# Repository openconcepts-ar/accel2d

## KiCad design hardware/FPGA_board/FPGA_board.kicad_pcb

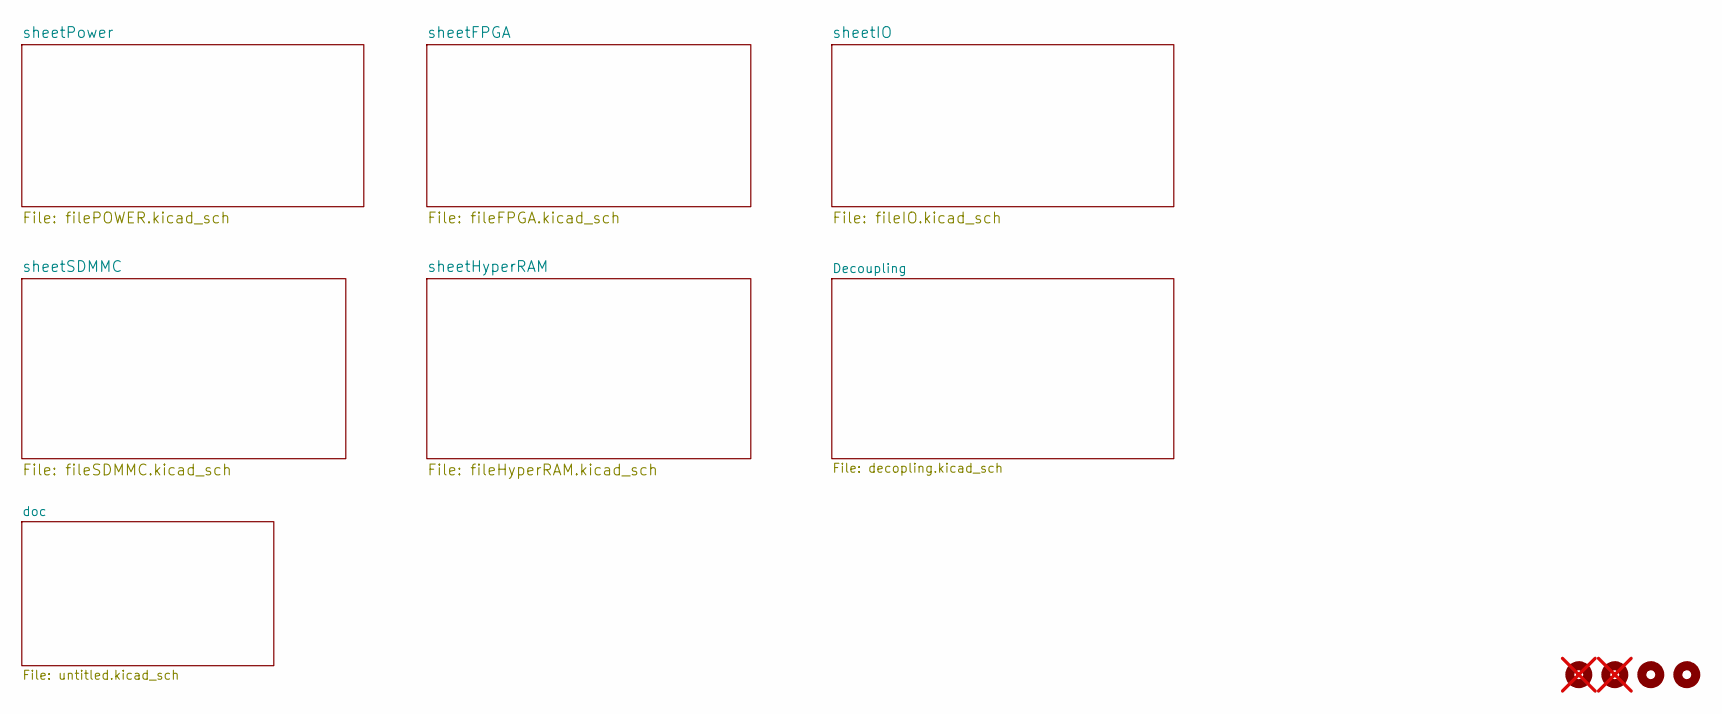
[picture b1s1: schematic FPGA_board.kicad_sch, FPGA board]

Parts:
H1, H2: MountingHole; MountingHole_2.2mm_M2_Pad; not fitted
H3, H4: MountingHole; MountingHole_2.1mm

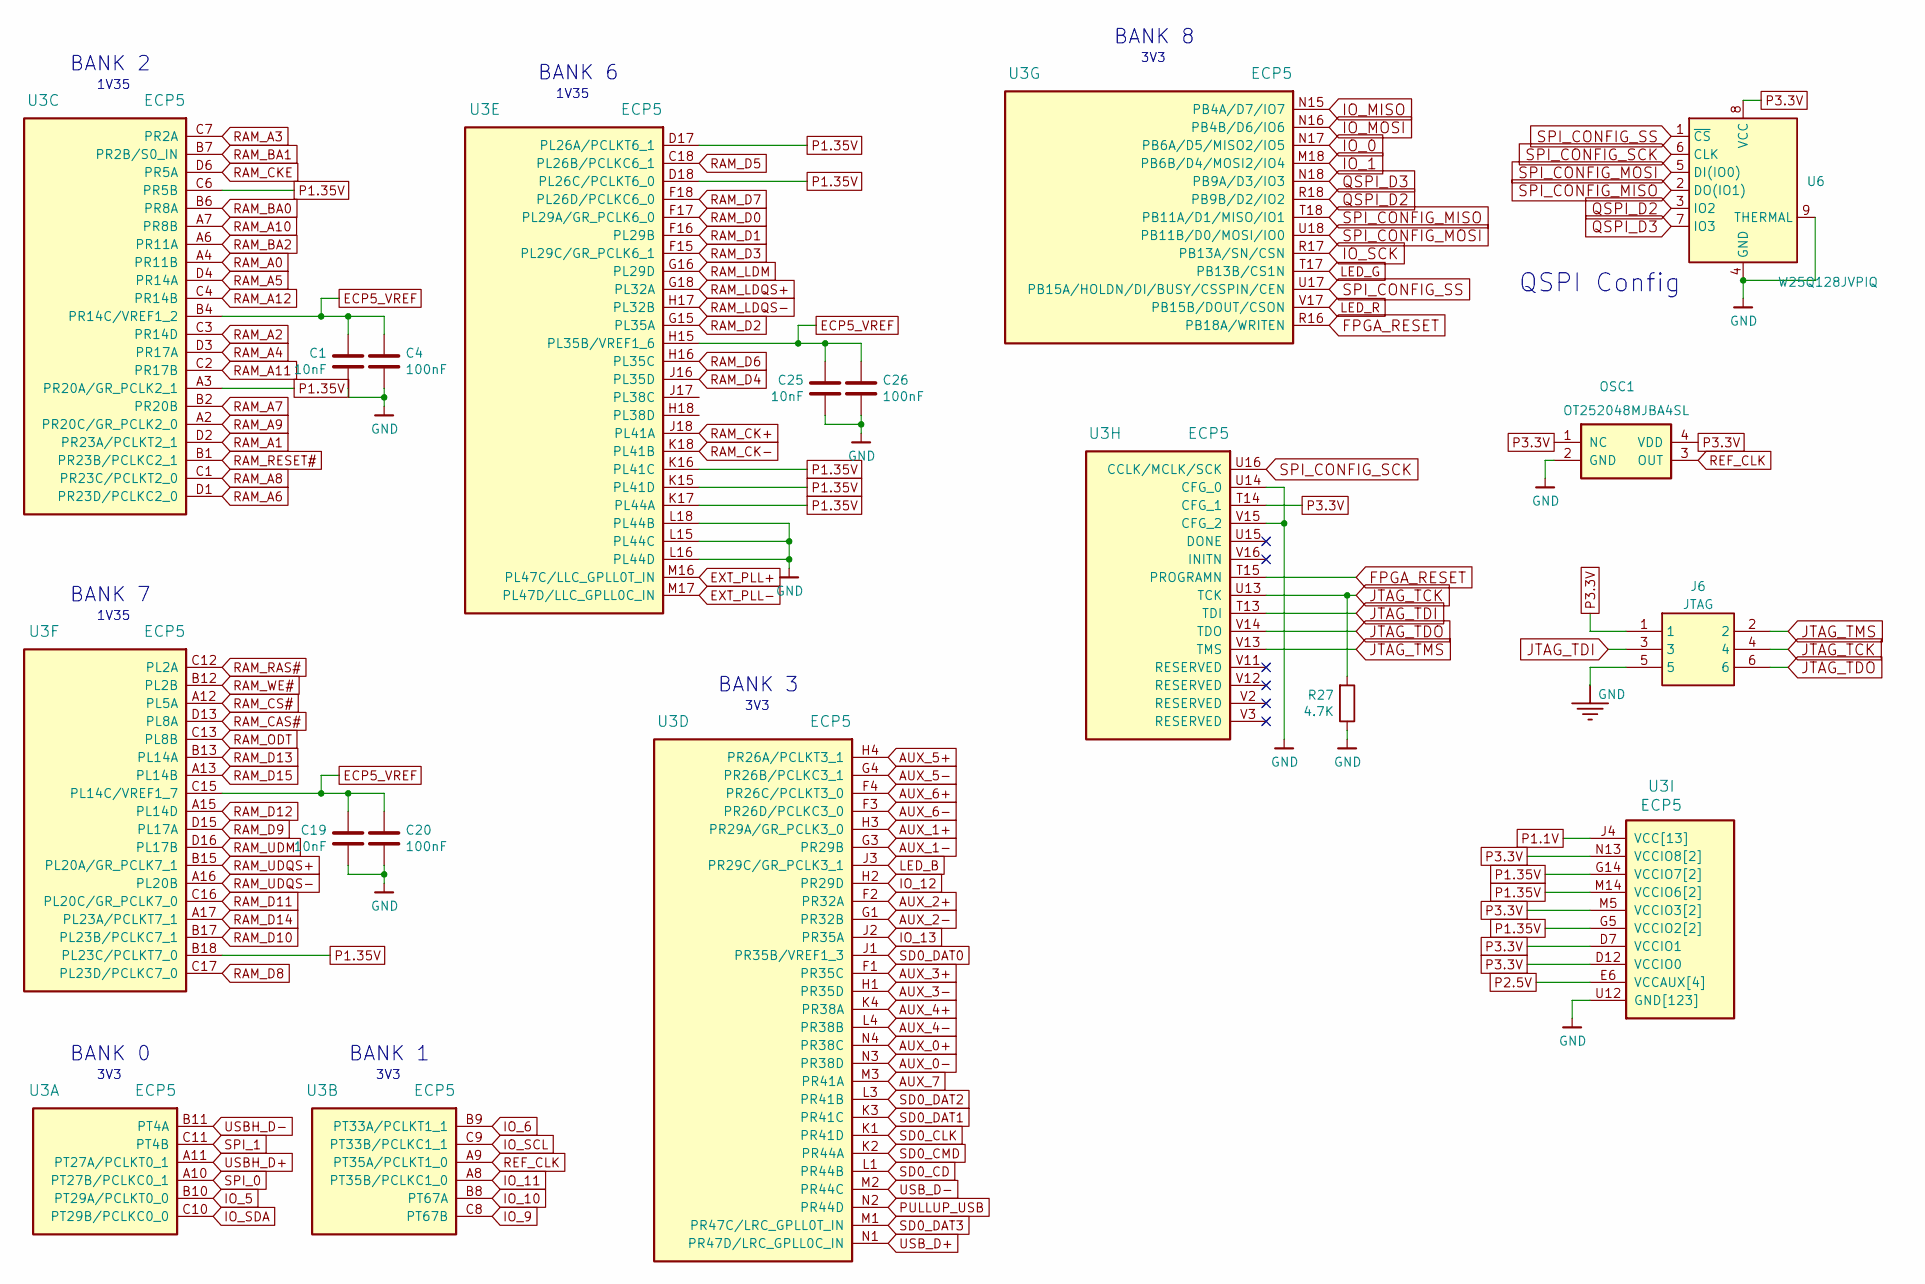
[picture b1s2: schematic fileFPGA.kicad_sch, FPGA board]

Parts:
C1, C19, C25: 10nF; C_0201_0603Metric; MPN GRM033R61C103KA12D
C4, C20, C26: 100nF; C_0201_0603Metric; MPN CL03A104KQ3NNNC
J6: JTAG; Tag-Connect_TC2030-IDC-NL_2x03_P1.27mm_Vertical; Mouser Part Number 474-PRT-12807; LCSC Part Number DNP
OSC1: OT252048MJBA4SL; Oscilator_2.5x2.0; MPN OT252048MJBA4SL
R27: 4.7K; R_0201_0603Metric; MPN RC0201FR-074K7L
U3: ECP5; csBGA285; MPN LFE5U-85F-8MG285I
U6: W25Q128JVPIQ; WSON-8-1EP_6x5mm_P1.27mm_EP3.4x4.3mm; MPN W25Q128JVPIQ

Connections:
AUX_0+: U3.N4 (PR38C); also elsewhere on the board
AUX_0-: U3.N3 (PR38D); also elsewhere on the board
AUX_1+: U3.H3 (PR29A/GR_PCLK3_0); also elsewhere on the board
AUX_1-: U3.G3 (PR29B); also elsewhere on the board
AUX_2+: U3.F2 (PR32A); also elsewhere on the board
AUX_2-: U3.G1 (PR32B); also elsewhere on the board
AUX_3+: U3.F1 (PR35C); also elsewhere on the board
AUX_3-: U3.H1 (PR35D); also elsewhere on the board
AUX_4+: U3.K4 (PR38A); also elsewhere on the board
AUX_4-: U3.L4 (PR38B); also elsewhere on the board
AUX_5+: U3.H4 (PR26A/PCLKT3_1); also elsewhere on the board
AUX_5-: U3.G4 (PR26B/PCLKC3_1); also elsewhere on the board
AUX_6+: U3.F4 (PR26C/PCLKT3_0); also elsewhere on the board
AUX_6-: U3.F3 (PR26D/PCLKC3_0); also elsewhere on the board
AUX_7: U3.M3 (PR41A); also elsewhere on the board
ECP5_VREF: C1.1, C4.1, C19.1, C20.1, C25.1, C26.1, U3.B4 (PR14C/VREF1_2), U3.C15 (PL14C/VREF1_7), U3.H15 (PL35B/VREF1_6); also elsewhere on the board
EXT_PLL+: U3.M16 (PL47C/LLC_GPLL0T_IN); also elsewhere on the board
EXT_PLL-: U3.M17 (PL47D/LLC_GPLL0C_IN); also elsewhere on the board
FPGA_RESET: U3.R16 (PB18A/WRITEN), U3.T15 (PROGRAMN); also elsewhere on the board
GND: C1.2, C4.2, C19.2, C20.2, C25.2, C26.2, J6.5, OSC1.2 (GND), R27.1, U3.B3 (GND[123]), U3.B16 (GND[123]), U3.E5 (GND[123]), U3.E7 (GND[123]), U3.E8 (GND[123]), U3.E9 (GND[123]), U3.E10 (GND[123]), U3.E11 (GND[123]), U3.E12 (GND[123]), U3.E14 (GND[123]), U3.F5 (GND[123]), U3.F6 (GND[123]), U3.F7 (GND[123]), U3.F8 (GND[123]), U3.F9 (GND[123]), U3.F10 (GND[123]), U3.F11 (GND[123]), U3.F12 (GND[123]), U3.F13 (GND[123]), U3.F14 (GND[123]), U3.G2 (GND[123]), U3.G6 (GND[123]), U3.G7 (GND[123]), U3.G8 (GND[123]), U3.G9 (GND[123]), U3.G10 (GND[123]), U3.G11 (GND[123]), U3.G12 (GND[123]), U3.G13 (GND[123]), U3.G17 (GND[123]), U3.H6 (GND[123]), U3.H7 (GND[123]), U3.H8 (GND[123]), U3.H9 (GND[123]), U3.H10 (GND[123]), U3.H11 (GND[123]), U3.H12 (GND[123]), U3.H13 (GND[123]), U3.J6 (GND[123]), U3.J7 (GND[123]), U3.J8 (GND[123]), U3.J9 (GND[123]), U3.J10 (GND[123]), U3.J11 (GND[123]), U3.J12 (GND[123]), U3.J13 (GND[123]), U3.K5 (GND[123]), U3.K6 (GND[123]), U3.K7 (GND[123]), U3.K8 (GND[123]), U3.K9 (GND[123]), U3.K10 (GND[123]), U3.K11 (GND[123]), U3.K12 (GND[123]), U3.K13 (GND[123]), U3.K14 (GND[123]), U3.L2 (GND[123]), U3.L5 (GND[123]), U3.L6 (GND[123]), U3.L7 (GND[123]), U3.L8 (GND[123]), U3.L9 (GND[123]), U3.L10 (GND[123]), U3.L11 (GND[123]), U3.L12 (GND[123]), U3.L13 (GND[123]), U3.L14 (GND[123]), U3.L15 (PL44C), U3.L16 (PL44D), U3.L17 (GND[123]), U3.L18 (PL44B), U3.M6 (GND[123]), U3.M7 (GND[123]), U3.M8 (GND[123]), U3.M9 (GND[123]), U3.M10 (GND[123]), U3.M11 (GND[123]), U3.M12 (GND[123]), U3.M13 (GND[123]), U3.N7 (GND[123]), U3.N8 (GND[123]), U3.N9 (GND[123]), U3.N10 (GND[123]), U3.N11 (GND[123]), U3.N12 (GND[123]), U3.P5 (GND[123]), U3.P6 (GND[123]), U3.P8 (GND[123]), U3.P10 (GND[123]), U3.P12 (GND[123]), U3.R1 (GND[123]), U3.R2 (GND[123]), U3.R3 (GND[123]), U3.R10 (GND[123]), U3.T1 (GND[123]), U3.T2 (GND[123]), U3.T3 (GND[123]), U3.T4 (GND[123]), U3.T5 (GND[123]), U3.T6 (GND[123]), U3.T7 (GND[123]), U3.T8 (GND[123]), U3.T9 (GND[123]), U3.T10 (GND[123]), U3.T11 (GND[123]), U3.T12 (GND[123]), U3.T16 (GND[123]), U3.U1 (GND[123]), U3.U2 (GND[123]), U3.U3 (GND[123]), U3.U4 (GND[123]), U3.U5 (GND[123]), U3.U6 (GND[123]), U3.U7 (GND[123]), U3.U8 (GND[123]), U3.U9 (GND[123]), U3.U10 (GND[123]), U3.U11 (GND[123]), U3.U12 (GND[123]), U3.U14 (CFG_0), U3.V4 (GND[123]), U3.V5 (GND[123]), U3.V6 (GND[123]), U3.V7 (GND[123]), U3.V8 (GND[123]), U3.V9 (GND[123]), U3.V10 (GND[123]), U3.V15 (CFG_2), U6.4 (GND), U6.9 (THERMAL); also elsewhere on the board
IO_0: U3.N17 (PB6A/D5/MISO2/IO5); also elsewhere on the board
IO_1: U3.M18 (PB6B/D4/MOSI2/IO4); also elsewhere on the board
IO_5: U3.B10 (PT29A/PCLKT0_0); also elsewhere on the board
IO_6: U3.B9 (PT33A/PCLKT1_1); also elsewhere on the board
IO_9: U3.C8 (PT67B); also elsewhere on the board
IO_10: U3.B8 (PT67A); also elsewhere on the board
IO_11: U3.A8 (PT35B/PCLKC1_0); also elsewhere on the board
IO_12: U3.H2 (PR29D); also elsewhere on the board
IO_13: U3.J2 (PR35A); also elsewhere on the board
IO_MISO: U3.N15 (PB4A/D7/IO7); also elsewhere on the board
IO_MOSI: U3.N16 (PB4B/D6/IO6); also elsewhere on the board
IO_SCK: U3.R17 (PB13A/SN/CSN); also elsewhere on the board
IO_SCL: U3.C9 (PT33B/PCLKC1_1); also elsewhere on the board
IO_SDA: U3.C10 (PT29B/PCLKC0_0); also elsewhere on the board
JTAG_TCK: J6.4, R27.2, U3.U13 (TCK)
JTAG_TDI: J6.3, U3.T13 (TDI)
JTAG_TDO: J6.6, U3.V14 (TDO)
JTAG_TMS: J6.2, U3.V13 (TMS)
LED_B: U3.J3 (PR29C/GR_PCLK3_1); also elsewhere on the board
LED_G: U3.T17 (PB13B/CS1N); also elsewhere on the board
LED_R: U3.V17 (PB15B/DOUT/CSON); also elsewhere on the board
P1.1V: U3.D8 (VCC[13]), U3.D9 (VCC[13]), U3.D10 (VCC[13]), U3.D11 (VCC[13]), U3.J4 (VCC[13]), U3.J5 (VCC[13]), U3.J14 (VCC[13]), U3.J15 (VCC[13]), U3.M4 (VCC[13]), U3.M15 (VCC[13]), U3.P7 (VCC[13]), U3.P9 (VCC[13]), U3.P11 (VCC[13]); also elsewhere on the board
P1.35V: U3.A3 (PR20A/GR_PCLK2_1), U3.B18 (PL23C/PCLKT7_0), U3.C6 (PR5B), U3.D17 (PL26A/PCLKT6_1), U3.D18 (PL26C/PCLKT6_0), U3.G5 (VCCIO2[2]), U3.G14 (VCCIO7[2]), U3.H5 (VCCIO2[2]), U3.H14 (VCCIO7[2]), U3.K15 (PL41D), U3.K16 (PL41C), U3.K17 (PL44A), U3.M14 (VCCIO6[2]), U3.N14 (VCCIO6[2]); also elsewhere on the board
P2.5V: U3.E6 (VCCAUX[4]), U3.E13 (VCCAUX[4]), U3.N6 (VCCAUX[4]), U3.P13 (VCCAUX[4]); also elsewhere on the board
P3.3V: J6.1, OSC1.1 (NC), OSC1.4 (VDD), U3.D7 (VCCIO1), U3.D12 (VCCIO0), U3.M5 (VCCIO3[2]), U3.N5 (VCCIO3[2]), U3.N13 (VCCIO8[2]), U3.P14 (VCCIO8[2]), U3.T14 (CFG_1), U6.8 (VCC); also elsewhere on the board
PULLUP_USB: U3.N2 (PR44D); also elsewhere on the board
QSPI_D2: U3.R18 (PB9B/D2/IO2), U6.3 (IO2)
QSPI_D3: U3.N18 (PB9A/D3/IO3), U6.7 (IO3)
RAM_A0: U3.A4 (PR11B); also elsewhere on the board
RAM_A1: U3.D2 (PR23A/PCLKT2_1); also elsewhere on the board
RAM_A2: U3.C3 (PR14D); also elsewhere on the board
RAM_A3: U3.C7 (PR2A); also elsewhere on the board
RAM_A4: U3.D3 (PR17A); also elsewhere on the board
RAM_A5: U3.D4 (PR14A); also elsewhere on the board
RAM_A6: U3.D1 (PR23D/PCLKC2_0); also elsewhere on the board
RAM_A7: U3.B2 (PR20B); also elsewhere on the board
RAM_A8: U3.C1 (PR23C/PCLKT2_0); also elsewhere on the board
RAM_A9: U3.A2 (PR20C/GR_PCLK2_0); also elsewhere on the board
RAM_A10: U3.A7 (PR8B); also elsewhere on the board
RAM_A11: U3.C2 (PR17B); also elsewhere on the board
RAM_A12: U3.C4 (PR14B); also elsewhere on the board
RAM_BA0: U3.B6 (PR8A); also elsewhere on the board
RAM_BA1: U3.B7 (PR2B/S0_IN); also elsewhere on the board
RAM_BA2: U3.A6 (PR11A); also elsewhere on the board
RAM_CAS#: U3.D13 (PL8A); also elsewhere on the board
RAM_CK+: U3.J18 (PL41A); also elsewhere on the board
RAM_CK-: U3.K18 (PL41B); also elsewhere on the board
RAM_CKE: U3.D6 (PR5A); also elsewhere on the board
RAM_CS#: U3.A12 (PL5A); also elsewhere on the board
RAM_D0: U3.F17 (PL29A/GR_PCLK6_0); also elsewhere on the board
RAM_D1: U3.F16 (PL29B); also elsewhere on the board
RAM_D2: U3.G15 (PL35A); also elsewhere on the board
RAM_D3: U3.F15 (PL29C/GR_PCLK6_1); also elsewhere on the board
RAM_D4: U3.J16 (PL35D); also elsewhere on the board
RAM_D5: U3.C18 (PL26B/PCLKC6_1); also elsewhere on the board
RAM_D6: U3.H16 (PL35C); also elsewhere on the board
RAM_D7: U3.F18 (PL26D/PCLKC6_0); also elsewhere on the board
RAM_D8: U3.C17 (PL23D/PCLKC7_0); also elsewhere on the board
RAM_D9: U3.D15 (PL17A); also elsewhere on the board
RAM_D10: U3.B17 (PL23B/PCLKC7_1); also elsewhere on the board
RAM_D11: U3.C16 (PL20C/GR_PCLK7_0); also elsewhere on the board
RAM_D12: U3.A15 (PL14D); also elsewhere on the board
RAM_D13: U3.B13 (PL14A); also elsewhere on the board
RAM_D14: U3.A17 (PL23A/PCLKT7_1); also elsewhere on the board
RAM_D15: U3.A13 (PL14B); also elsewhere on the board
RAM_LDM: U3.G16 (PL29D); also elsewhere on the board
RAM_LDQS+: U3.G18 (PL32A); also elsewhere on the board
RAM_LDQS-: U3.H17 (PL32B); also elsewhere on the board
RAM_ODT: U3.C13 (PL8B); also elsewhere on the board
RAM_RAS#: U3.C12 (PL2A); also elsewhere on the board
RAM_RESET#: U3.B1 (PR23B/PCLKC2_1); also elsewhere on the board
RAM_UDM: U3.D16 (PL17B); also elsewhere on the board
RAM_UDQS+: U3.B15 (PL20A/GR_PCLK7_1); also elsewhere on the board
RAM_UDQS-: U3.A16 (PL20B); also elsewhere on the board
RAM_WE#: U3.B12 (PL2B); also elsewhere on the board
REF_CLK: OSC1.3 (OUT), U3.A9 (PT35A/PCLKT1_0)
SD0_CD: U3.L1 (PR44B); also elsewhere on the board
SD0_CLK: U3.K1 (PR41D); also elsewhere on the board
SD0_CMD: U3.K2 (PR44A); also elsewhere on the board
SD0_DAT0: U3.J1 (PR35B/VREF1_3); also elsewhere on the board
SD0_DAT1: U3.K3 (PR41C); also elsewhere on the board
SD0_DAT2: U3.L3 (PR41B); also elsewhere on the board
SD0_DAT3: U3.M1 (PR47C/LRC_GPLL0T_IN); also elsewhere on the board
SPI_0: U3.A10 (PT27B/PCLKC0_1); also elsewhere on the board
SPI_1: U3.C11 (PT4B); also elsewhere on the board
SPI_CONFIG_MISO: U3.T18 (PB11A/D1/MISO/IO1), U6.2 (DO(IO1))
SPI_CONFIG_MOSI: U3.U18 (PB11B/D0/MOSI/IO0), U6.5 (DI(IO0))
SPI_CONFIG_SCK: U3.U16 (CCLK/MCLK/SCK), U6.6 (CLK)
SPI_CONFIG_SS: U3.U17 (PB15A/HOLDN/DI/BUSY/CSSPIN/CEN), U6.1 (~CS)
USBH_D+: U3.A11 (PT27A/PCLKT0_1); also elsewhere on the board
USBH_D-: U3.B11 (PT4A); also elsewhere on the board
USB_D+: U3.N1 (PR47D/LRC_GPLL0C_IN); also elsewhere on the board
USB_D-: U3.M2 (PR44C); also elsewhere on the board

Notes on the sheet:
BANK 0
3V3
BANK 1
1V35
BANK 6
BANK 7
BANK 3
3V3
1V35
QSPI Config
BANK 8
BANK 2

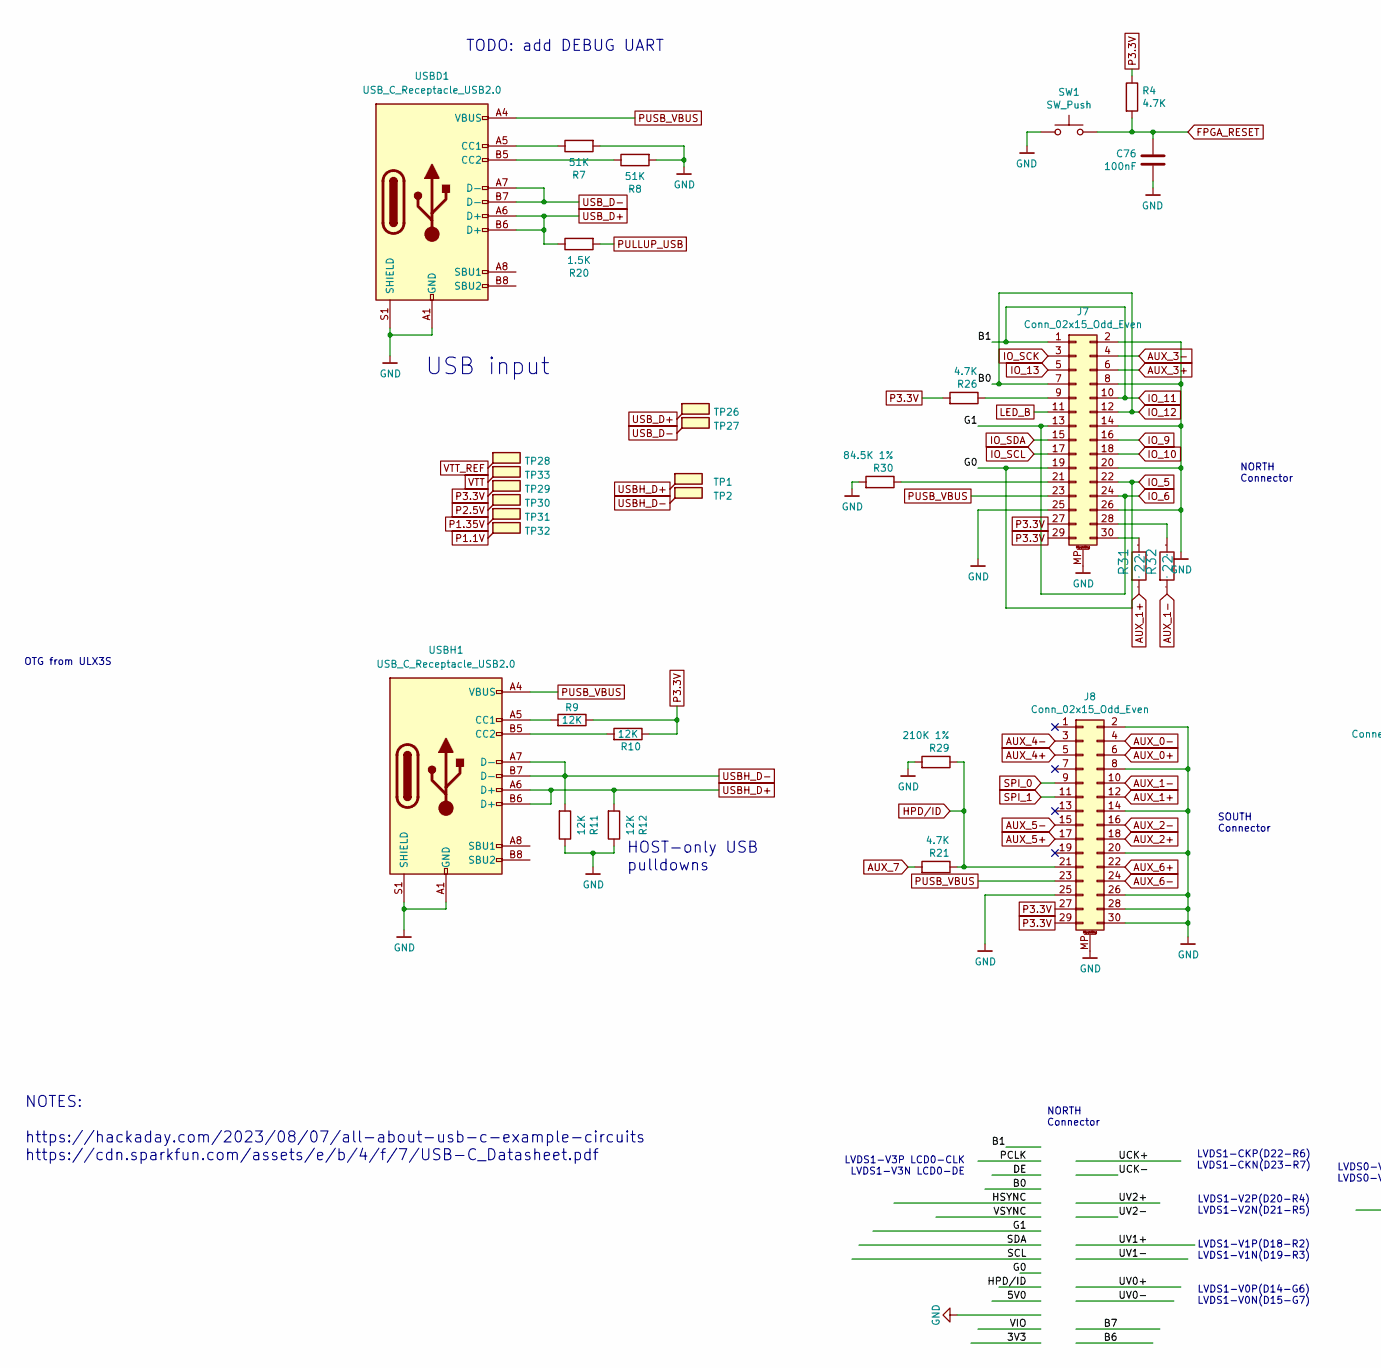
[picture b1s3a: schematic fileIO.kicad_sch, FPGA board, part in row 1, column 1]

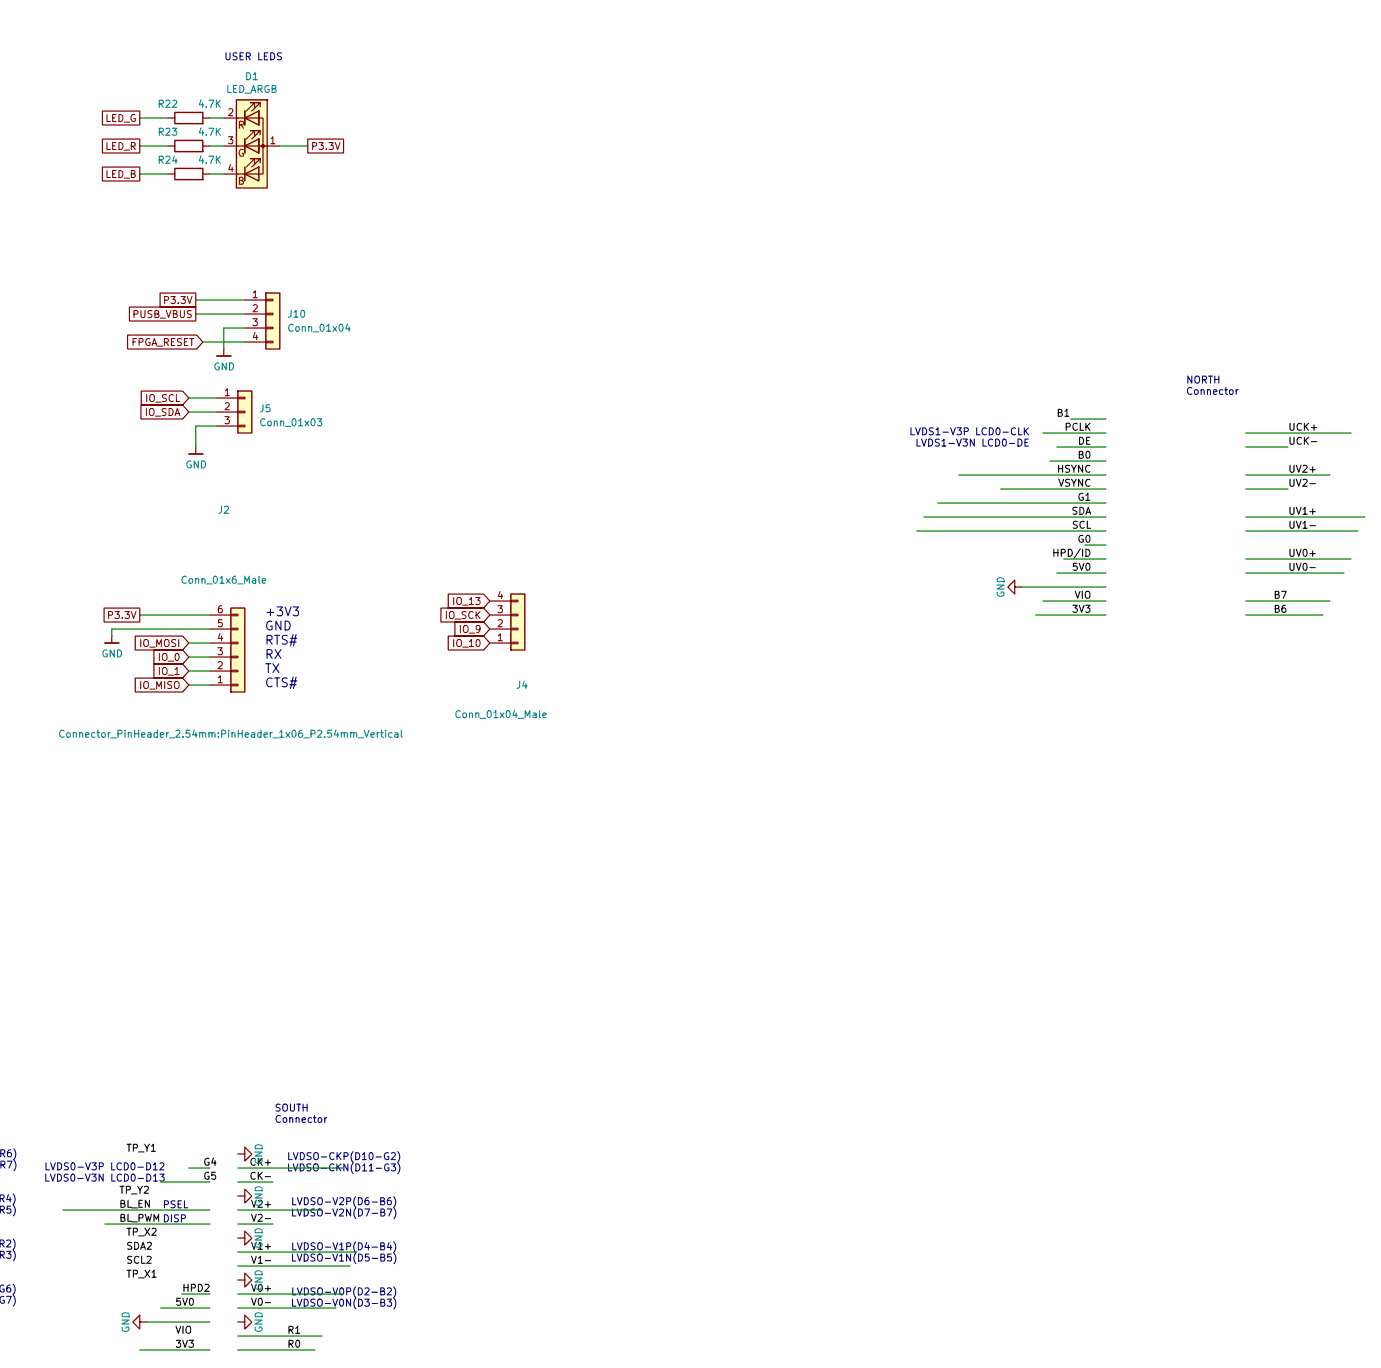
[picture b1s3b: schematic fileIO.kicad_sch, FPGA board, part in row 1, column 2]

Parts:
C76: 100nF; C_0201_0603Metric; MPN CL03A104KQ3NNNC
D1: LED_ARGB; 0404LED_RGB; MPN MHPA1010RGBDT
J2: Conn_01x6_Male; PinHeader_1x06_P2.54mm_Vertical
J4: Conn_01x04_Male; PinHeader_1x04_P2.54mm_Vertical
J5: Conn_01x03; PinHeader_1x03_P2.54mm_Vertical
J7, J8: Conn_02x15_Odd_Even; DF12NB3030DP05V51; MPN DF12NB(3.0)-30DS-0.5V(51)
J10: Conn_01x04; PinHeader_1x04_P2.54mm_Vertical
R4, R21, R22, R23, R24, R26: 4.7K; R_0201_0603Metric; MPN RC0201FR-074K7L
R7, R8: 51K; R_0201_0603Metric
R9, R10, R11, R12: 12K; R_0201_0603Metric
R20: 1.5K; R_0201_0603Metric; MPN RC0201FR-071K5L
R29: 210K 1%; R_0402_1005Metric; MPN 0402WGF2103TCE
R30: 84.5K 1%; R_0201_0603Metric
R31, R32: 22; R_0402_1005Metric
SW1: SW_Push; SW_SPST_PTS810; MPN PTS810SJM250SMTRLFS
TP1, TP2, TP26, TP27: SMD_TP; TestPoint_Pad_D1.0mm
TP28, TP29, TP30, TP31, TP32, TP33: SMD_TP; TestPoint_Pad_D0.5mm
USBD1: USB_C_Receptacle_USB2.0; USB_C_Receptacle_G-Switch_GT-USB-7010ASV; MPN GT-USB-7010ASV
USBH1: USB_C_Receptacle_USB2.0; USB_C_Receptacle_G-Switch_GT-USB-7010ASV; MPN GT-USB-7010ASV

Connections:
AUX_0+: J8.6; also elsewhere on the board
AUX_0-: J8.4; also elsewhere on the board
AUX_1+: J8.12, R31.2; also elsewhere on the board
AUX_1-: J8.10, R32.2; also elsewhere on the board
AUX_2+: J8.18; also elsewhere on the board
AUX_2-: J8.16; also elsewhere on the board
AUX_3+: J7.6; also elsewhere on the board
AUX_3-: J7.4; also elsewhere on the board
AUX_4+: J8.5; also elsewhere on the board
AUX_4-: J8.3; also elsewhere on the board
AUX_5+: J8.17; also elsewhere on the board
AUX_5-: J8.15; also elsewhere on the board
AUX_6+: J8.22; also elsewhere on the board
AUX_6-: J8.24; also elsewhere on the board
AUX_7: R21.2; also elsewhere on the board
FPGA_RESET: C76.1, J10.4, R4.2, SW1.2; also elsewhere on the board
GND: C76.2, J2.5, J5.3, J7.2, J7.8, J7.14, J7.20, J7.25, J7.26, J7.MP (MountPin), J8.2, J8.8, J8.14, J8.20, J8.25, J8.26, J8.28, J8.30, J8.MP (MountPin), J10.3, R7.2, R8.2, R11.1, R12.1, R29.2, R30.2, SW1.1, USBD1.A1 (GND), USBD1.A12 (GND), USBD1.B1 (GND), USBD1.B12 (GND), USBD1.S1 (SHIELD), USBH1.A1 (GND), USBH1.A12 (GND), USBH1.B1 (GND), USBH1.B12 (GND), USBH1.S1 (SHIELD); also elsewhere on the board
HPD/ID: J8.21, R21.1, R29.1
IO_0: J2.3; also elsewhere on the board
IO_1: J2.2; also elsewhere on the board
IO_5: J7.19, J7.22; also elsewhere on the board
IO_6: J7.13, J7.24; also elsewhere on the board
IO_9: J4.2, J7.16; also elsewhere on the board
IO_10: J4.1, J7.18; also elsewhere on the board
IO_11: J7.1, J7.10; also elsewhere on the board
IO_12: J7.7, J7.12; also elsewhere on the board
IO_13: J4.4, J7.5; also elsewhere on the board
IO_MISO: J2.1; also elsewhere on the board
IO_MOSI: J2.4; also elsewhere on the board
IO_SCK: J4.3, J7.3; also elsewhere on the board
IO_SCL: J5.1, J7.17; also elsewhere on the board
IO_SDA: J5.2, J7.15; also elsewhere on the board
LED_B: J7.11, R24.1; also elsewhere on the board
LED_G: R22.1; also elsewhere on the board
LED_R: R23.1; also elsewhere on the board
unnamed: D1.4 (BK), R24.2
unnamed: D1.3 (GK), R23.2
unnamed: D1.2 (RK), R22.2
unnamed: J7.9, R26.1
unnamed: J7.21, R30.1
unnamed: J7.28, R32.1
unnamed: J7.30, R31.1
unnamed: R7.1, USBD1.A5 (CC1)
unnamed: R8.1, USBD1.B5 (CC2)
unnamed: R9.2, USBH1.A5 (CC1)
unnamed: R10.2, USBH1.B5 (CC2)
P1.1V: TP32.1; also elsewhere on the board
P1.35V: TP31.1; also elsewhere on the board
P2.5V: TP30.1; also elsewhere on the board
P3.3V: D1.1 (A), J2.6, J7.27, J7.29, J8.27, J8.29, J10.1, R4.1, R9.1, R10.1, R26.2, TP29.1; also elsewhere on the board
PULLUP_USB: R20.2; also elsewhere on the board
PUSB_VBUS: J7.23, J8.23, J10.2, USBD1.A4 (VBUS), USBD1.A9 (VBUS), USBD1.B4 (VBUS), USBD1.B9 (VBUS), USBH1.A4 (VBUS), USBH1.A9 (VBUS), USBH1.B4 (VBUS), USBH1.B9 (VBUS); also elsewhere on the board
SPI_0: J8.9; also elsewhere on the board
SPI_1: J8.11; also elsewhere on the board
USBH_D+: R12.2, TP1.1, USBH1.A6 (D+), USBH1.B6 (D+); also elsewhere on the board
USBH_D-: R11.2, TP2.1, USBH1.A7 (D-), USBH1.B7 (D-); also elsewhere on the board
USB_D+: R20.1, TP26.1, USBD1.A6 (D+), USBD1.B6 (D+); also elsewhere on the board
USB_D-: TP27.1, USBD1.A7 (D-), USBD1.B7 (D-); also elsewhere on the board
VTT: TP33.1; also elsewhere on the board
VTT_REF: TP28.1; also elsewhere on the board

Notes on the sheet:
LVDSO-CKP(D10-G2) LVDSO-CKN(D11-G3) LVDSO-V2P(D6-B6) LVDSO-V2N(D7-B7) LVDSO-V1P(D4-B4) LVDSO-V1N(D5-B5) LVDSO-V0P(D2-B2) LVDSO-V0N(D3-B3)
NORTH Connector
TODO: add DEBUG UART
USB input
SOUTH Connector
HOST-only USB pulldowns
LVDS0-V3P LCD0-D12 LVDS0-V3N LCD0-D13
+3V3 GND RTS# RX TX CTS#
LVDS1-V3P LCD0-CLK LVDS1-V3N LCD0-DE
LVDS1-CKP(D22-R6) LVDS1-CKN(D23-R7) LVDS1-V2P(D20-R4) LVDS1-V2N(D21-R5) LVDS1-V1P(D18-R2) LVDS1-V1N(D19-R3) LVDS1-V0P(D14-G6) LVDS1-V0N(D15-G7)
NOTES: https://hackaday.com/2023/08/07/all-about-usb-c-example-circuits https://cdn.sparkfun.com/assets/e/b/4/f/7/USB-C_Datasheet.pdf
USER LEDS
OTG from ULX3S
PSEL
DISP

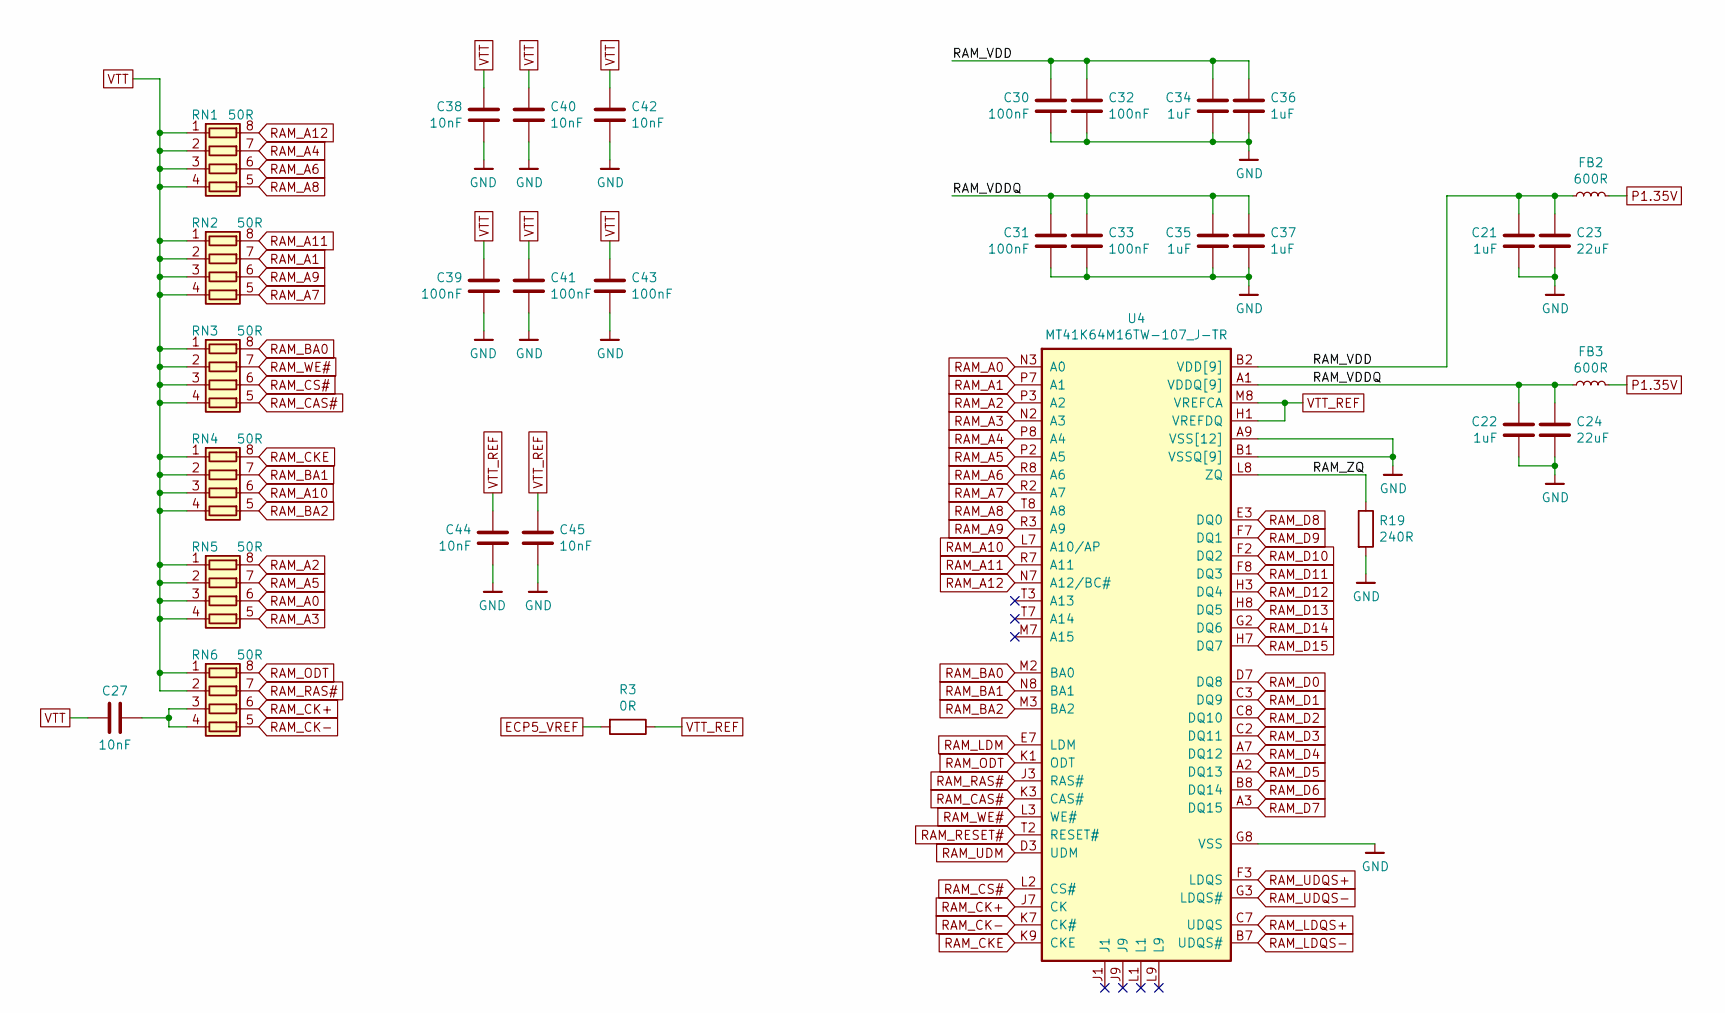
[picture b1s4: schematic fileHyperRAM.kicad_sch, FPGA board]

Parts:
C21, C22, C34, C35, C36, C37: 1uF; C_0402_1005Metric; MPN JMK105C6105KV-F
C23, C24: 22uF; C_0603_1608Metric; MPN GRM188R60J226MEA0D
C27, C38, C40, C42, C44, C45: 10nF; C_0201_0603Metric; MPN GRM033R61C103KA12D
C30, C31, C32, C33, C39, C41, C43: 100nF; C_0201_0603Metric; MPN CL03A104KQ3NNNC
FB2, FB3: 600R; L_0402_1005Metric; MPN BLM15AG601SN1D
R3: 0R; R_0201_0603Metric; MPN RC0201FR-070RL
R19: 240R; R_0402_1005Metric; MPN RC0402FR-07240RL
RN1, RN2, RN3, RN4, RN5, RN6: 50R; R_Array_Convex_4x0402; MPN WA04X49R9FTL
U4: MT41K64M16TW-107_J-TR; BGA-96_9.0x13.0mm_Layout2x3x16_P0.8mm; MPN MT41K64M16TW-107:J TR

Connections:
/sheetHyperRAM/RAM_VDD: C21.1, C23.1, C30.1, C32.1, C34.1, C36.1, FB2.1, U4.B2 (VDD[9]), U4.D9 (VDD), U4.G7 (VDD), U4.K2 (VDD), U4.K8 (VDD), U4.N1 (VDD), U4.N9 (VDD), U4.R1 (VDD), U4.R9 (VDD)
/sheetHyperRAM/RAM_VDDQ: C22.1, C24.1, C31.1, C33.1, C35.1, C37.1, FB3.1, U4.A1 (VDDQ[9]), U4.A8 (VDDQ), U4.C1 (VDDQ), U4.C9 (VDDQ), U4.D2 (VDDQ), U4.E9 (VDDQ), U4.F1 (VDDQ), U4.H2 (VDDQ), U4.H9 (VDDQ)
/sheetHyperRAM/RAM_ZQ: R19.1, U4.L8 (ZQ)
ECP5_VREF: R3.2; also elsewhere on the board
GND: C21.2, C22.2, C23.2, C24.2, C30.2, C31.2, C32.2, C33.2, C34.2, C35.2, C36.2, C37.2, C38.1, C39.1, C40.1, C41.1, C42.1, C43.1, C44.1, C45.1, R19.2, U4.A9 (VSS[12]), U4.B1 (VSSQ[9]), U4.B3 (VSS), U4.B9 (VSSQ), U4.D1 (VSSQ), U4.D8 (VSSQ), U4.E1 (VSS), U4.E2 (VSSQ), U4.E8 (VSSQ), U4.F9 (VSSQ), U4.G1 (VSSQ), U4.G8 (VSS), U4.G9 (VSSQ), U4.J2 (VSS), U4.J8 (VSS), U4.M1 (VSS), U4.M9 (VSS), U4.P1 (VSS), U4.P9 (VSS), U4.T1 (VSS), U4.T9 (VSS); also elsewhere on the board
unnamed: C27.1, RN6.3 (R3.1), RN6.4 (R4.1)
P1.35V: FB2.2, FB3.2; also elsewhere on the board
RAM_A0: RN5.6 (R3.2), U4.N3 (A0); also elsewhere on the board
RAM_A1: RN2.7 (R2.2), U4.P7 (A1); also elsewhere on the board
RAM_A2: RN5.8 (R1.2), U4.P3 (A2); also elsewhere on the board
RAM_A3: RN5.5 (R4.2), U4.N2 (A3); also elsewhere on the board
RAM_A4: RN1.7 (R2.2), U4.P8 (A4); also elsewhere on the board
RAM_A5: RN5.7 (R2.2), U4.P2 (A5); also elsewhere on the board
RAM_A6: RN1.6 (R3.2), U4.R8 (A6); also elsewhere on the board
RAM_A7: RN2.5 (R4.2), U4.R2 (A7); also elsewhere on the board
RAM_A8: RN1.5 (R4.2), U4.T8 (A8); also elsewhere on the board
RAM_A9: RN2.6 (R3.2), U4.R3 (A9); also elsewhere on the board
RAM_A10: RN4.6 (R3.2), U4.L7 (A10/AP); also elsewhere on the board
RAM_A11: RN2.8 (R1.2), U4.R7 (A11); also elsewhere on the board
RAM_A12: RN1.8 (R1.2), U4.N7 (A12/BC#); also elsewhere on the board
RAM_BA0: RN3.8 (R1.2), U4.M2 (BA0); also elsewhere on the board
RAM_BA1: RN4.7 (R2.2), U4.N8 (BA1); also elsewhere on the board
RAM_BA2: RN4.5 (R4.2), U4.M3 (BA2); also elsewhere on the board
RAM_CAS#: RN3.5 (R4.2), U4.K3 (CAS#); also elsewhere on the board
RAM_CK+: RN6.6 (R3.2), U4.J7 (CK); also elsewhere on the board
RAM_CK-: RN6.5 (R4.2), U4.K7 (CK#); also elsewhere on the board
RAM_CKE: RN4.8 (R1.2), U4.K9 (CKE); also elsewhere on the board
RAM_CS#: RN3.6 (R3.2), U4.L2 (CS#); also elsewhere on the board
RAM_D0: U4.D7 (DQ8); also elsewhere on the board
RAM_D1: U4.C3 (DQ9); also elsewhere on the board
RAM_D2: U4.C8 (DQ10); also elsewhere on the board
RAM_D3: U4.C2 (DQ11); also elsewhere on the board
RAM_D4: U4.A7 (DQ12); also elsewhere on the board
RAM_D5: U4.A2 (DQ13); also elsewhere on the board
RAM_D6: U4.B8 (DQ14); also elsewhere on the board
RAM_D7: U4.A3 (DQ15); also elsewhere on the board
RAM_D8: U4.E3 (DQ0); also elsewhere on the board
RAM_D9: U4.F7 (DQ1); also elsewhere on the board
RAM_D10: U4.F2 (DQ2); also elsewhere on the board
RAM_D11: U4.F8 (DQ3); also elsewhere on the board
RAM_D12: U4.H3 (DQ4); also elsewhere on the board
RAM_D13: U4.H8 (DQ5); also elsewhere on the board
RAM_D14: U4.G2 (DQ6); also elsewhere on the board
RAM_D15: U4.H7 (DQ7); also elsewhere on the board
RAM_LDM: U4.E7 (LDM); also elsewhere on the board
RAM_LDQS+: U4.C7 (UDQS); also elsewhere on the board
RAM_LDQS-: U4.B7 (UDQS#); also elsewhere on the board
RAM_ODT: RN6.8 (R1.2), U4.K1 (ODT); also elsewhere on the board
RAM_RAS#: RN6.7 (R2.2), U4.J3 (RAS#); also elsewhere on the board
RAM_RESET#: U4.T2 (RESET#); also elsewhere on the board
RAM_UDM: U4.D3 (UDM); also elsewhere on the board
RAM_UDQS+: U4.F3 (LDQS); also elsewhere on the board
RAM_UDQS-: U4.G3 (LDQS#); also elsewhere on the board
RAM_WE#: RN3.7 (R2.2), U4.L3 (WE#); also elsewhere on the board
VTT: C27.2, C38.2, C39.2, C40.2, C41.2, C42.2, C43.2, RN1.1 (R1.1), RN1.2 (R2.1), RN1.3 (R3.1), RN1.4 (R4.1), RN2.1 (R1.1), RN2.2 (R2.1), RN2.3 (R3.1), RN2.4 (R4.1), RN3.1 (R1.1), RN3.2 (R2.1), RN3.3 (R3.1), RN3.4 (R4.1), RN4.1 (R1.1), RN4.2 (R2.1), RN4.3 (R3.1), RN4.4 (R4.1), RN5.1 (R1.1), RN5.2 (R2.1), RN5.3 (R3.1), RN5.4 (R4.1), RN6.1 (R1.1), RN6.2 (R2.1); also elsewhere on the board
VTT_REF: C44.2, C45.2, R3.1, U4.H1 (VREFDQ), U4.M8 (VREFCA); also elsewhere on the board

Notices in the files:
hardware/FPGA_board/FPGA_board.kicad_sch:
(C) 2023-2026 Victor Suarez Rovere
﻿CERN Open Hardware Licence v1.2
hardware/LVDS_DVI_adapter/LVDS_DVI_adapter.kicad_pcb:
Copyright (C) Victor Suarez Rovere
License:  CERN OHL-S
hardware/LVDS_DVI_adapter/LVDS_DVI_adapter.kicad_sch:
Copyright (C) 2023-2024 Victor Suarez Rovere
hardware/LVDS_adapter/LVDS_adapter.kicad_pcb:
CERN OHL-S license
